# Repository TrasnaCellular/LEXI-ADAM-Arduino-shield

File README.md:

"# LEXI-ADAM-Arduino-Shield: This is still a placeholder as the design is in progress: the whole project will be uploaded/updated almost on a daily basis until the board is produced"

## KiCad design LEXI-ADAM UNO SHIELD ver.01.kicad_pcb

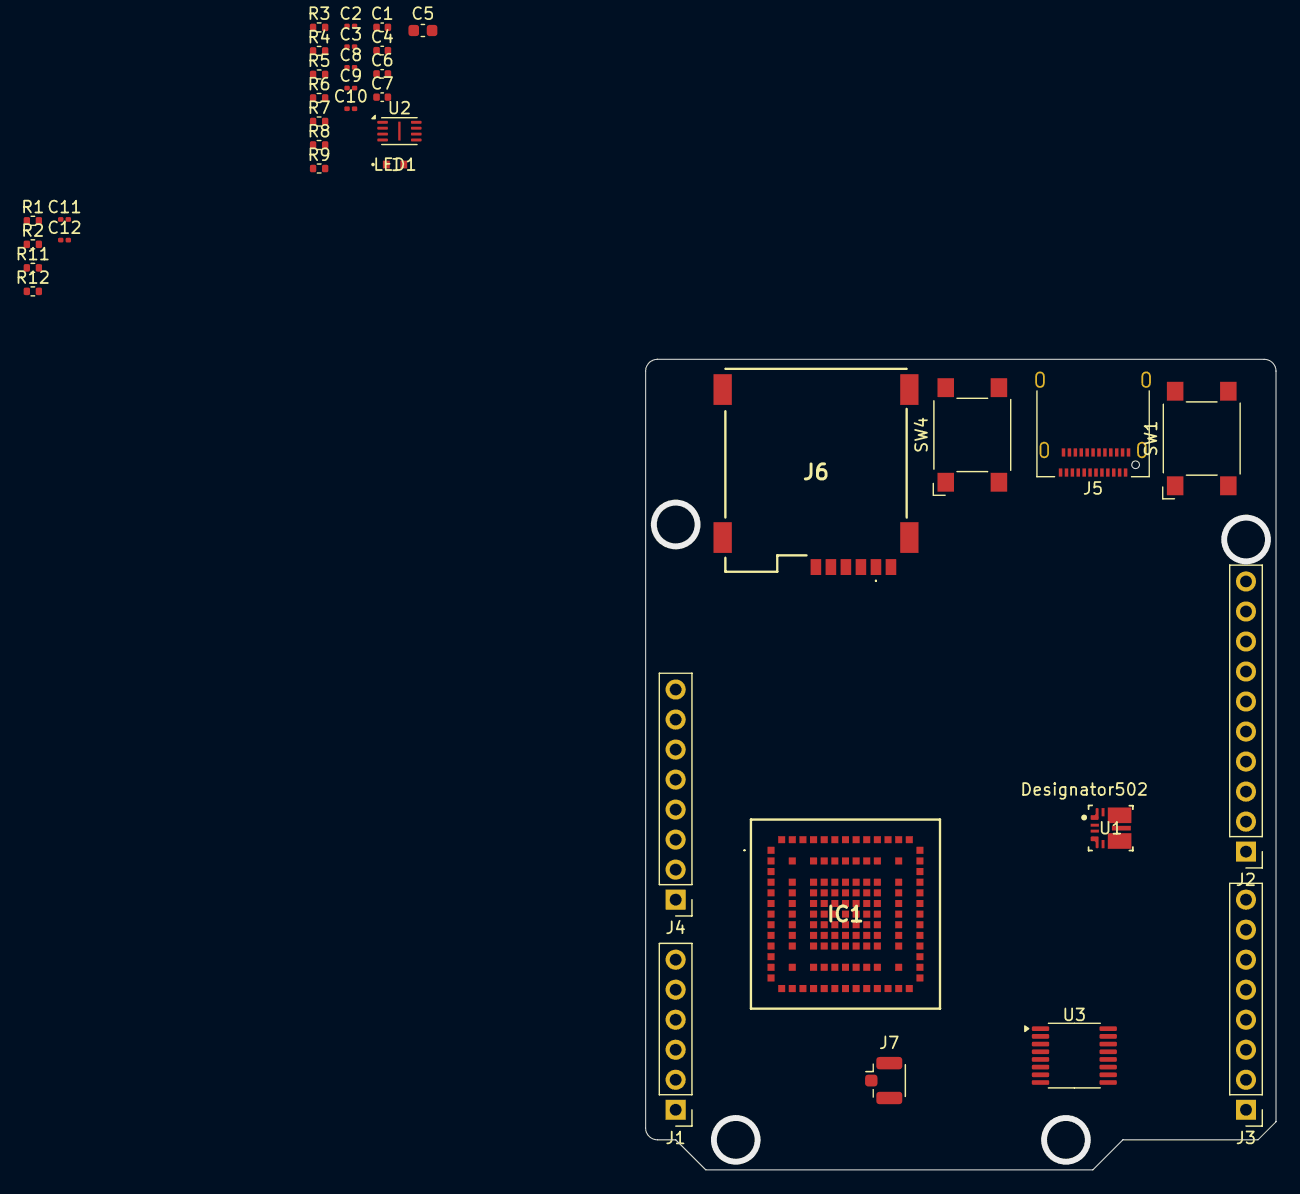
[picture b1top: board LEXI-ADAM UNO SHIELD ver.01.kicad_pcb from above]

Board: 4 copper layers, 53.3 x 68.6 mm, 37 parts (0 on the bottom side), 23 nets, no tracks yet.

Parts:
C1: 4U7 10V; C_0402_1005Metric
C2: 220N 10V; C_0201_0603Metric
C3, C8, C9, C10: 33P 50V; C_0201_0603Metric
C4, C7: 2N2 16V; C_0402_1005Metric
C5: 22u 10V; C_0603_1608Metric
C6: 10u 10V; C_0402_1005Metric
C11, C12: 100N 10V; C_0201_0603Metric
IC1: LEXI-R10801D-00B-00; LEXIR10801D00B00
J1: SSW-106-03-G-S
J2: SSW-110-03-G-S; SSW-110-03-L-S
J3, J4: SSW-108-03-G-S
J5: USB_C_Receptacle; USB_C_Receptacle_Amphenol_12401610E4-2A
J6: MSIM-2-A; MSIM2A
J7: Conn_Coaxial; U.FL_Hirose_U.FL-R-SMT-1_Vertical
LED1: LTST-S270TGKT; LED_LTST-S270TGKT_LTO-L
R1, R2, R3, R4, R8, R11, R12: 10K 1%; R_0402_1005Metric
R5: 1M8 1%; R_0402_1005Metric
R6: 270K 1%; R_0402_1005Metric
R7: 180R 5%; R_0402_1005Metric
R9: 1K5 5%; R_0402_1005Metric
SW1, SW4: B3FS-1000P; SW_SPST_Omron_B3FS-100xP
U1: TPSM828303ARDSR; RDS0009A-MFG
U2: APS1604M-3SQRx-ZR; Winbond_USON-8-1EP_3x2mm_P0.5mm_EP0.2x1.6mm
U3: SN74AVC4T245PW; TSSOP-16_4.4x5mm_P0.65mm

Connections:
3V3: J4.5, R1.2
5V: C1.1, C4.1, J4.4, J5.A4 (VBUS), J5.A9 (VBUS), J5.B4 (VBUS), J5.B9 (VBUS), R3.1, U1.1 (VIN)
CELL_RXD: IC1.4 (RXD), U3.11 (2B1)
CELL_TXD: IC1.5 (TXD), U3.13 (1B1)
D0_USART1_RX: J3.1, U3.6 (2A1)
D1_USART1_TX: J3.2, U3.4 (1A1)
GND: C1.2, C2.2, C3.2, C4.2, C5.2, C6.2, C7.2, C8.2, C9.2, C10.1, C11.1, C12.2, J4.2, J4.3, LED1.1, R2.2, R4.2, R6.2, R9.2, R11.2, R12.2, U1.2 (GND), U3.8 (GND), U3.9 (GND)
IOREF: C11.2, J4.7, U3.1 (VCCA)
unnamed: J5.A1 (GND), J5.A12 (GND), J5.B1 (GND), J5.B12 (GND)
unnamed: LED1.2, R7.2
unnamed: R5.2, R6.1, U1.4 (FB)
unnamed: R3.2, R4.1, U1.3 (MODE)
unnamed: R2.1, U3.2 (1DIR)
unnamed: R12.1, U3.15 (1~OE)
unnamed: R1.1, U3.3 (2DIR)
unnamed: R11.1, U3.14 (2~OE)
SIM_CLK: C9.1, IC1.31 (SIM_CLK), J6.C3 (CLK)
SIM_IO: C10.2, IC1.32 (SIM_IO), J6.C7 (I/O)
SIM_RST: C8.1, IC1.30 (SIM_RST), J6.C2 (RST)
SIM_VCC: C2.1, C3.1, IC1.33 (VSIM), J6.C1 (VCC)
VCC: C5.1, C6.1, C7.1, R5.1, R7.1, U1.6 (VOUT)
VCC_EN: R8.2, R9.1, U1.9 (EN)
V_INT: C12.1, IC1.43 (V_INT), U3.16 (VCCB)

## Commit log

2026-01-09 test commit
2026-01-09 test commit 2
2026-01-09 test commit 3
2026-01-09 test commit 4
